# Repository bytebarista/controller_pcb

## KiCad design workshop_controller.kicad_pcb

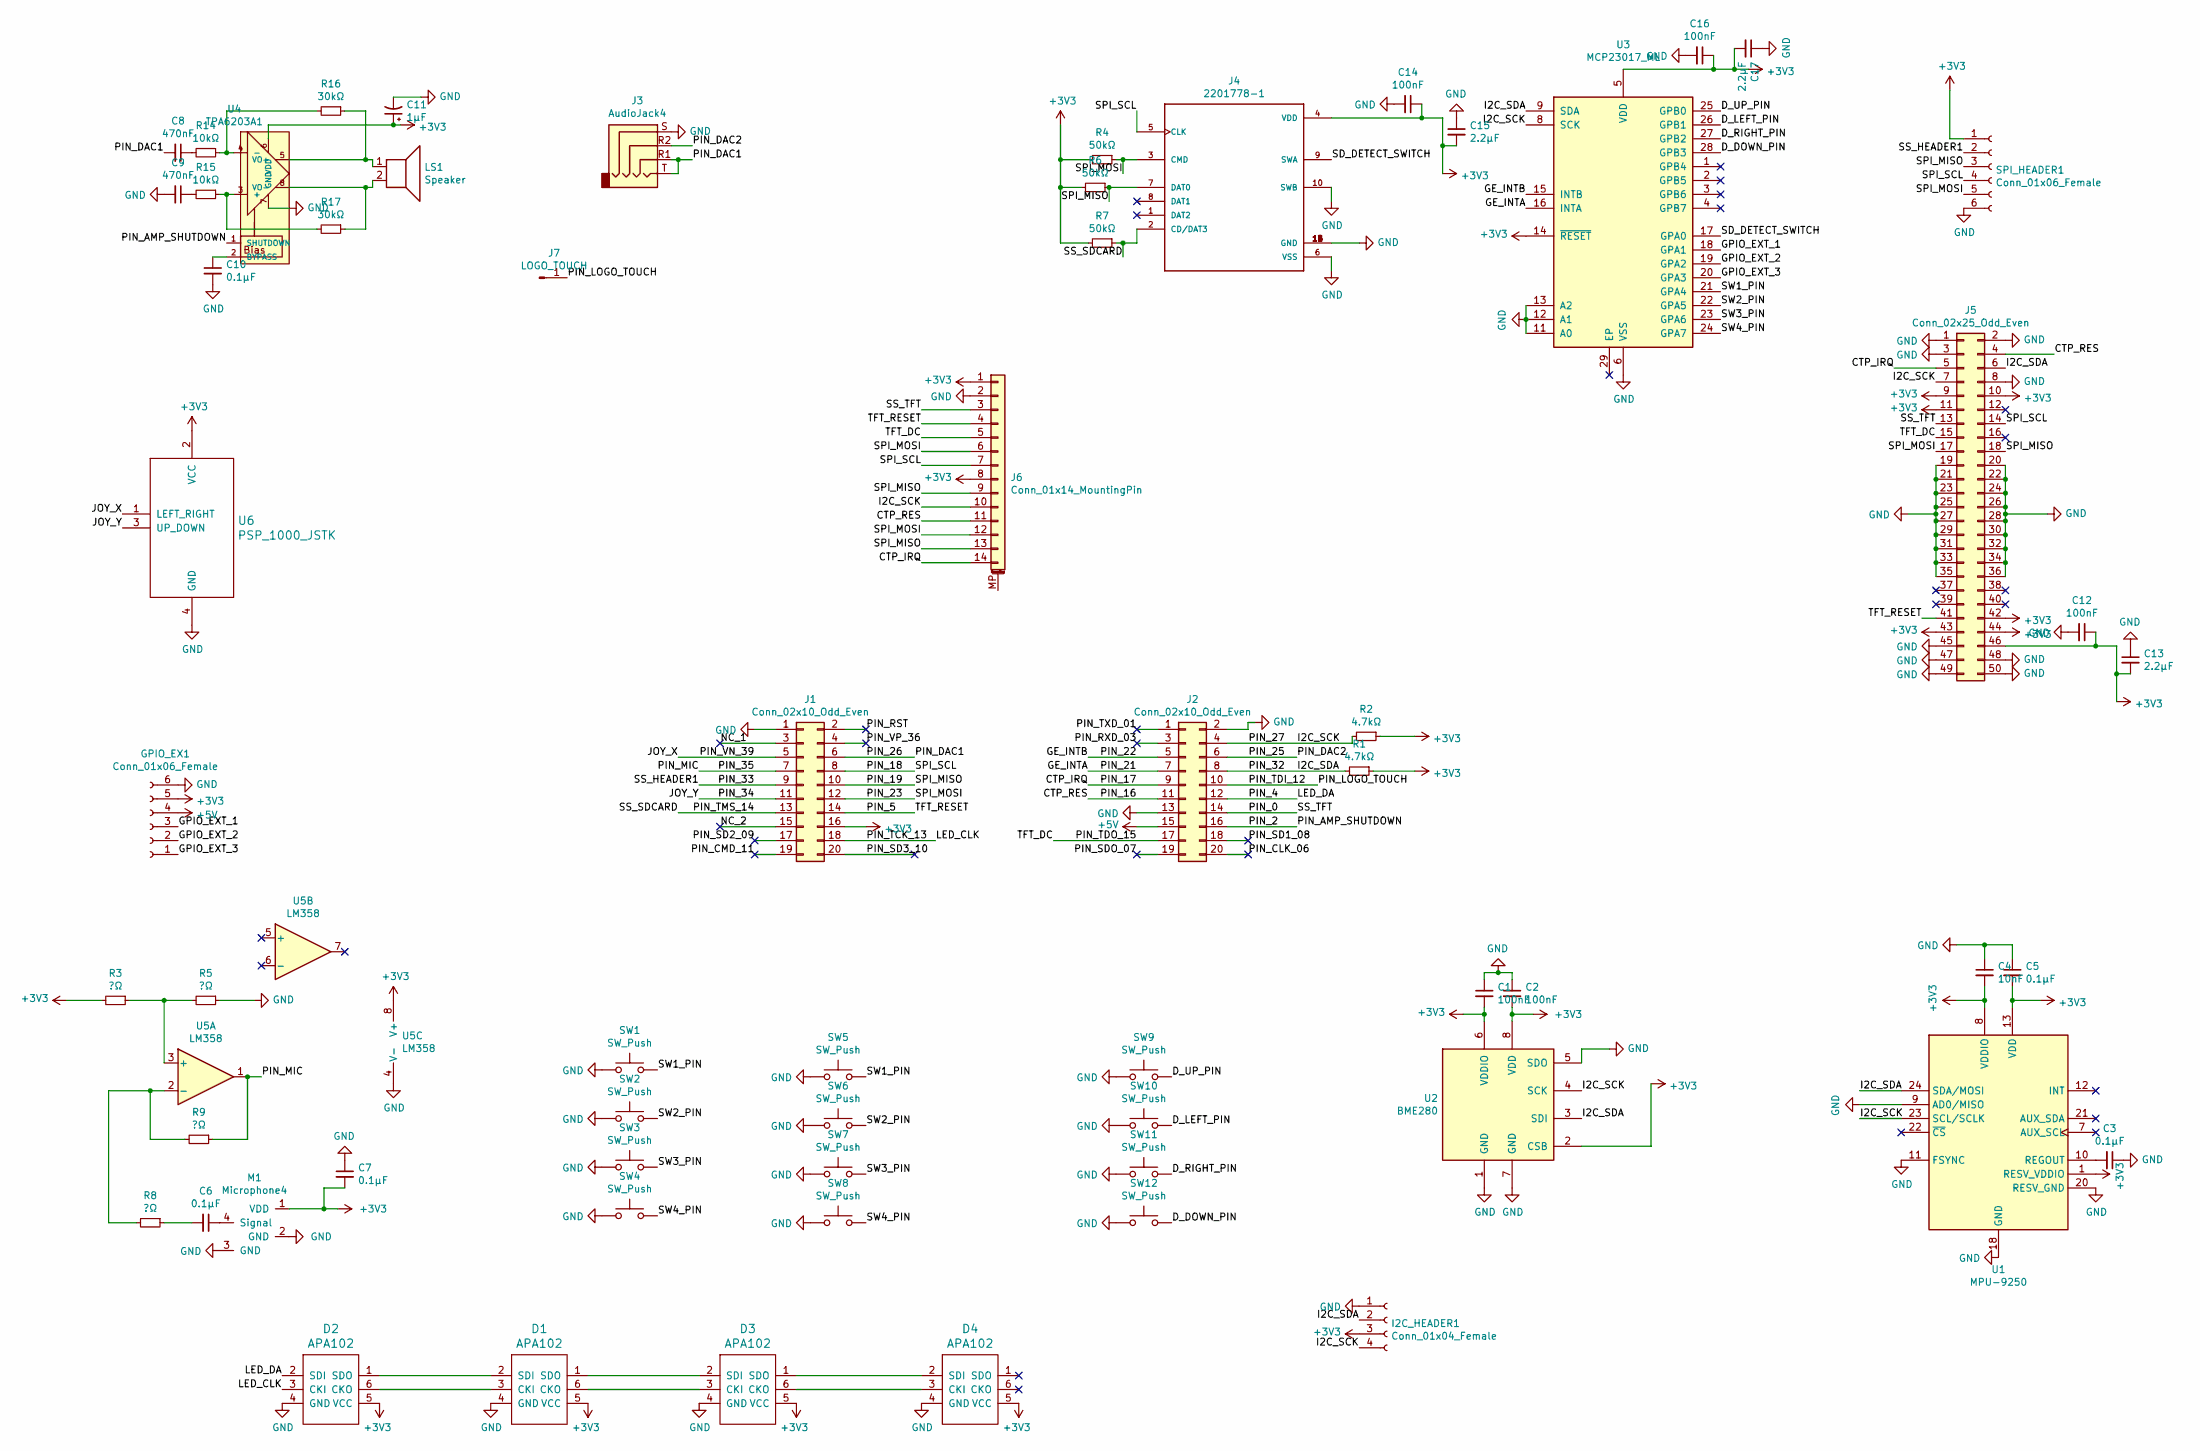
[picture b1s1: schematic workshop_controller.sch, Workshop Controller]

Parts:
C1, C2, C12, C14, C16: 100nF; C_0603_1608Metric_Pad1.05x0.95mm_HandSolder
C3, C5, C6, C7, C10: 0.1µF; C_0603_1608Metric_Pad1.05x0.95mm_HandSolder
C4: 10nF; C_0603_1608Metric_Pad1.05x0.95mm_HandSolder
C8, C9: 470nF; C_0603_1608Metric_Pad1.05x0.95mm_HandSolder
C11: 1µF; C_0603_1608Metric_Pad1.05x0.95mm_HandSolder
C13, C15, C17: 2.2µF; C_0603_1608Metric_Pad1.05x0.95mm_HandSolder
D1, D2, D3, D4: APA102; APA102-2020
GPIO_EX1: Conn_01x06_Female; PinSocket_2x03_P2.54mm_Vertical_SMD
I2C_HEADER1: Conn_01x04_Female; PinSocket_2x03_P2.54mm_Vertical_SMD
J1, J2: Conn_02x10_Odd_Even; PinHeader_2x10_P2.54mm_Vertical_SMD
J3: AudioJack4; Jack_3.5mm_PJ320D_Horizontal
J4: 2201778-1; TE_2201778-1microsd
J5: Conn_02x25_Odd_Even; Hirose_FH12-50S-0.5SH_1x50-1MP_P0.50mm_Horizontal
J6: Conn_01x14_MountingPin; PinHeader_1x14_P2.54mm_Vertical
J7: LOGO_TOUCH; LOGO_SMD
LS1: Speaker; Speaker_SMD_CUI
M1: Microphone4; CMM-3125AT-42316-TR
R1, R2: 4.7kΩ; R_0603_1608Metric_Pad1.05x0.95mm_HandSolder
R3, R5, R8, R9: ?Ω; R_0603_1608Metric_Pad1.05x0.95mm_HandSolder
R4, R6, R7: 50kΩ; R_0603_1608Metric_Pad1.05x0.95mm_HandSolder
R14, R15: 10kΩ; R_0603_1608Metric_Pad1.05x0.95mm_HandSolder
R16, R17: 30kΩ; R_0603_1608Metric_Pad1.05x0.95mm_HandSolder
SPI_HEADER1: Conn_01x06_Female; PinSocket_2x03_P2.54mm_Vertical_SMD
SW1, SW2, SW3, SW4: SW_Push; SW_PUSH-12mm_Wuerth-430476085716
SW5, SW6, SW7, SW8, SW9, SW10, SW11, SW12: SW_Push; contact_snes_button
U1: MPU-9250; QFN-24-1EP_3x3mm_P0.4mm_EP1.75x1.6mm
U2: BME280; Bosch_LGA-8_2.5x2.5mm_P0.65mm_ClockwisePinNumbering
U3: MCP23017_ML; QFN-28-1EP_6x6mm_P0.65mm_EP4.25x4.25mm
U4: TPA6203A1; MSOP-8-1EP_3x3mm_P0.65mm_EP1.68x1.88mm
U5: LM358; MSOP-8_3x3mm_P0.65mm
U6: PSP_1000_JSTK; JOYSTICK-PSP1000-THROUGHHOLE

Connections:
+3V3: C1.2, C2.2, C4.2, C5.2, C7.2, C11.1, C12.1, C13.2, C14.1, C15.2, C16.1, C17.2, D1.5 (VCC), D2.5 (VCC), D3.5 (VCC), D4.5 (VCC), GPIO_EX1.5, I2C_HEADER1.3, J1.16, J4.4 (VDD), J5.9, J5.10, J5.11, J5.42, J5.43, J5.44, J5.46, J6.1, J6.8, M1.1 (VDD), R1.1, R2.1, R3.2, R4.2, R6.2, R7.2, SPI_HEADER1.1, U1.1 (RESV_VDDIO), U1.8 (VDDIO), U1.13 (VDD), U2.2 (CSB), U2.6 (VDDIO), U2.8 (VDD), U3.5 (VDD), U3.14 (~RESET~), U4.6 (VDD), U5.8 (V+), U6.2 (VCC)
+5V: GPIO_EX1.4, J2.15
/CTP_IRQ: J2.9, J5.5, J6.14
/CTP_RES: J2.11, J5.4, J6.11
/D_DOWN_PIN: SW12.2, U3.28 (GPB3)
/D_LEFT_PIN: SW10.2, U3.26 (GPB1)
/D_RIGHT_PIN: SW11.2, U3.27 (GPB2)
/D_UP_PIN: SW9.2, U3.25 (GPB0)
/GE_INTA: J2.7, U3.16 (INTA)
/GE_INTB: J2.5, U3.15 (INTB)
/GPIO_EXT_1: GPIO_EX1.3, U3.18 (GPA1)
/GPIO_EXT_2: GPIO_EX1.2, U3.19 (GPA2)
/GPIO_EXT_3: GPIO_EX1.1, U3.20 (GPA3)
/I2C_SCK: I2C_HEADER1.4, J2.4, J5.7, J6.10, R2.2, U1.23 (SCL/SCLK), U2.4 (SCK), U3.8 (SCK)
/I2C_SDA: I2C_HEADER1.2, J2.8, J5.6, R1.2, U1.24 (SDA/MOSI), U2.3 (SDI), U3.9 (SDA)
/JOY_X: J1.5, U6.1 (LEFT_RIGHT)
/JOY_Y: J1.11, U6.3 (UP_DOWN)
/LED_CLK: D2.3 (CKI), J1.18
/LED_DA: D2.2 (SDI), J2.12
/NC_1: J1.3
/NC_2: J1.15
/PIN_0: J2.14, J5.13, J6.3
/PIN_2: J2.16, U4.1 (SHUTDOWN)
/PIN_5: J1.14, J5.41, J6.4
/PIN_18: J1.8, J4.5 (CLK), J5.14, J6.7, SPI_HEADER1.4
/PIN_19: J1.10, J4.7 (DAT0), J5.18, J6.9, J6.13, R6.1, SPI_HEADER1.3
/PIN_23: J1.12, J4.3 (CMD), J5.17, J6.6, J6.12, R4.1, SPI_HEADER1.5
/PIN_25: J2.6, J3.R2
/PIN_26: C8.2, J1.6, J3.R1, J3.T
/PIN_33: J1.9, SPI_HEADER1.2
/PIN_35: J1.7, R9.1, U5.1
/PIN_CLK_06: J2.20
/PIN_CMD_11: J1.19
/PIN_LOGO_TOUCH: J2.10, J7.1
/PIN_RST: J1.2
/PIN_RXD_03: J2.3
/PIN_SD1_08: J2.18
/PIN_SD2_09: J1.17
/PIN_SD3_10: J1.20
/PIN_SDO_07: J2.19
/PIN_TDO_15: J2.17, J5.15, J6.5
/PIN_TMS_14: J1.13, J4.2 (CD/DAT3), R7.1
/PIN_TXD_01: J2.1
/PIN_VP_36: J1.4
/SD_DETECT_SWITCH: J4.9 (SWA), U3.17 (GPA0)
/SW1_PIN: SW1.2, SW5.2, U3.21 (GPA4)
/SW2_PIN: SW2.2, SW6.2, U3.22 (GPA5)
/SW3_PIN: SW3.2, SW7.2, U3.23 (GPA6)
/SW4_PIN: SW4.2, SW8.2, U3.24 (GPA7)
GND: C1.1, C2.1, C3.1, C4.1, C5.1, C7.1, C9.2, C10.2, C11.2, C12.2, C13.1, C14.2, C15.1, C16.2, C17.1, D1.4 (GND), D2.4 (GND), D3.4 (GND), D4.4 (GND), GPIO_EX1.6, I2C_HEADER1.1, J1.1, J2.2, J2.13, J3.S, J4.6 (VSS), J4.10 (SWB), J4.11 (GND), J4.12 (GND), J4.13 (GND), J4.14 (GND), J4.15 (GND), J4.16 (GND), J5.1, J5.2, J5.3, J5.8, J5.19, J5.20, J5.21, J5.22, J5.23, J5.24, J5.25, J5.26, J5.27, J5.28, J5.29, J5.30, J5.31, J5.32, J5.33, J5.34, J5.35, J5.36, J5.45, J5.47, J5.48, J5.49, J5.50, J6.2, M1.2 (GND), M1.3 (GND), R5.1, SPI_HEADER1.6, SW1.1, SW2.1, SW3.1, SW4.1, SW5.1, SW6.1, SW7.1, SW8.1, SW9.1, SW10.1, SW11.1, SW12.1, U1.9 (AD0/MISO), U1.11 (FSYNC), U1.18 (GND), U1.20 (RESV_GND), U2.1 (GND), U2.5 (SDO), U2.7 (GND), U3.6 (VSS), U3.11 (A0), U3.12 (A1), U3.13 (A2), U4.7 (GND), U5.4 (V-), U6.4 (GND)
unnamed: C3.2, U1.10 (REGOUT)
unnamed: C6.1, M1.4 (Signal)
unnamed: C6.2, R8.1
unnamed: C8.1, R14.2
unnamed: C9.1, R15.2
unnamed: C10.1, U4.2 (BYPASS)
unnamed: D1.1 (SDO), D3.2 (SDI)
unnamed: D1.2 (SDI), D2.1 (SDO)
unnamed: D1.3 (CKI), D2.6 (CKO)
unnamed: D1.6 (CKO), D3.3 (CKI)
unnamed: D3.1 (SDO), D4.2 (SDI)
unnamed: D3.6 (CKO), D4.3 (CKI)
unnamed: LS1.1, R16.1, U4.5 (VO+)
unnamed: LS1.2, R17.1, U4.8 (VO-)
unnamed: R3.1, R5.2, U5.3 (+)
unnamed: R8.2, R9.2, U5.2 (-)
unnamed: R14.1, R16.2, U4.4 (-)
unnamed: R15.1, R17.2, U4.3 (+)

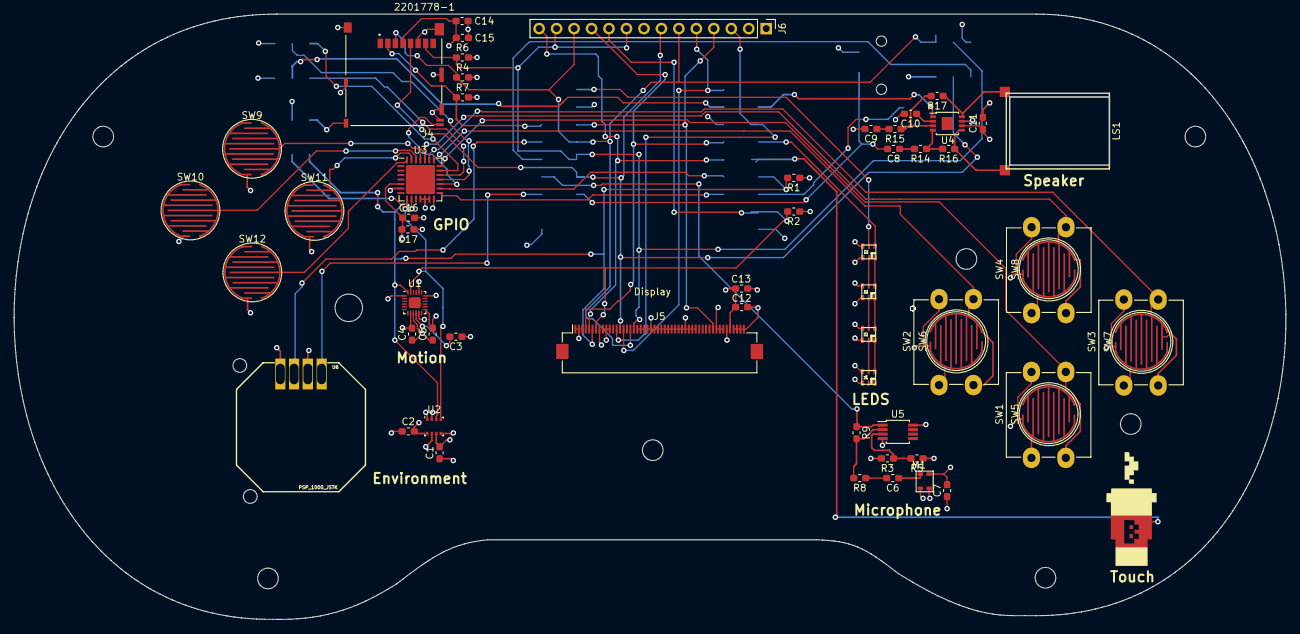
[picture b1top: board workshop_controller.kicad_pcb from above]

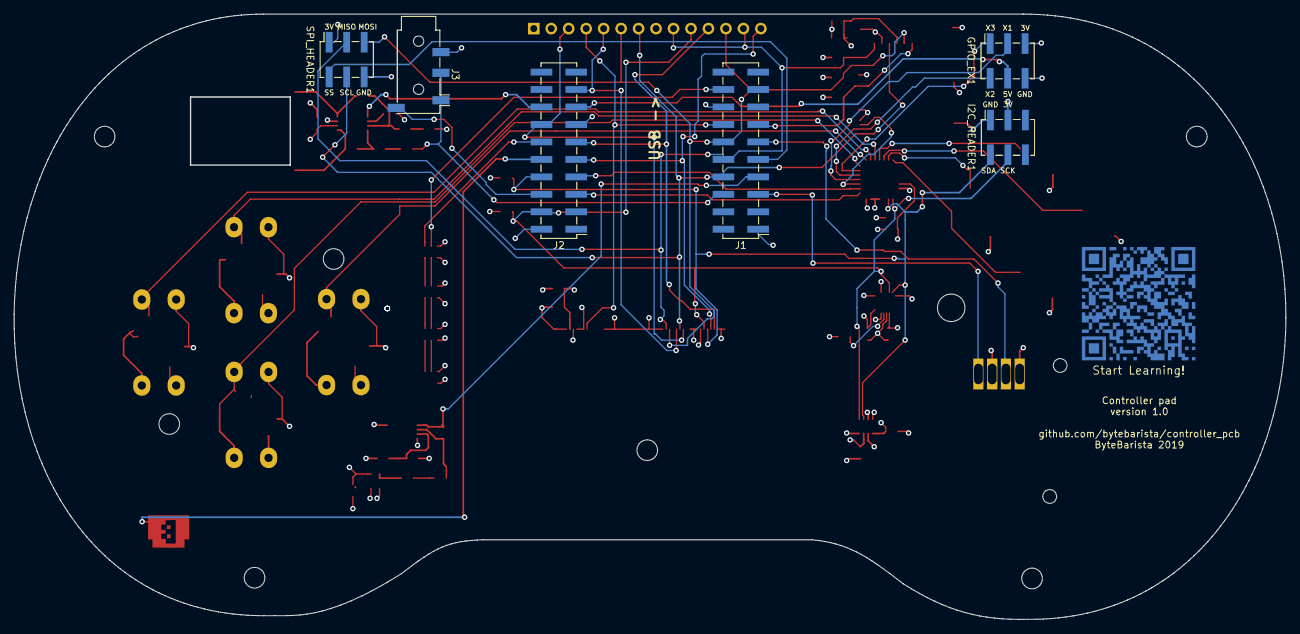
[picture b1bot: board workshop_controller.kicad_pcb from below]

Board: 4 copper layers, 184.9 x 88.0 mm, 66 parts (7 on the bottom side), 56 nets.

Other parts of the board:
Display: Display
Start Learning!: qr_bytebarista

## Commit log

2019-04-04 Add a few components
2019-04-04 Add some footprints
2019-04-04 Aesthetic changes
2019-04-05 Add TFT Display connector
2019-04-05 Use correct symbol for FFC
2019-04-07 Connect mpu9250
2019-04-07 connect bme280
2019-04-07 add outline
2019-04-07 Add labels
2019-04-08 Add opamp for mic preamp
2019-04-09 Add microphone circuit
2019-04-13 Add bytebarista lib
2019-04-15 Unstage project file
2019-04-15 Wire BME280
2019-04-15 Update schematic
2019-04-15 Wire components
2019-04-15 Add project file again
2019-04-16 Unknown changes
2019-04-16 Remove cache file
2019-04-16 Connect mpu9250, speaker circuit and gpio extender
2019-04-21 Add 2020 led
2019-04-21 Add tracks for prototype^C
2019-04-21 Fix LED tracks
2019-04-23 Add edge cuts
2019-04-23 Add cache
2019-04-23 Fix tracks
2019-04-23 Rotate display connector
2019-04-23 Move display connector
2019-04-24 Small changes
2019-04-25 Fix merge conflict
2019-04-25 Add tracks
2019-04-25 Add ground
2019-04-25 Fix rogue track
2019-04-26 Add tracks for gpio extender
2019-04-26 Add ground pour
2019-04-29 Label resistors and capacitors
2019-05-12 Add readme
2019-05-15 Fix microphone amp circuit
2019-05-15 Swap resistors
2019-05-15 Fix display circuit
2019-05-15 Do design rules check
2019-05-15 Resolve I2C addresses
2019-05-15 Change R3-R7 footprints to 0603
2019-05-15 Add pin numbers to esp32
2019-05-15 Change SPI header CS to 33
2019-05-15 Change a bunch of pins
2019-05-15 Move I2C pullup pins closer to esp32
2019-05-15 Swap SPI_SDI and SPI_SDO
2019-05-16 Use smd headers
2019-05-16 Redesign layout
2019-05-16 move esp32 headers closer together
2019-05-16 Move header pins
2019-05-18 Morten says: all is well
2019-05-20 Morten saves the day for prototype v0.2
2019-05-21 Add QR code
2019-05-21 Perform electrical rules check
2019-05-21 Make ready for production
2019-05-21 Hopefully nothing important
2019-07-03 Add footprints
2019-07-04 Add bom
2019-07-04 update gitignore
2019-07-04 update bom
